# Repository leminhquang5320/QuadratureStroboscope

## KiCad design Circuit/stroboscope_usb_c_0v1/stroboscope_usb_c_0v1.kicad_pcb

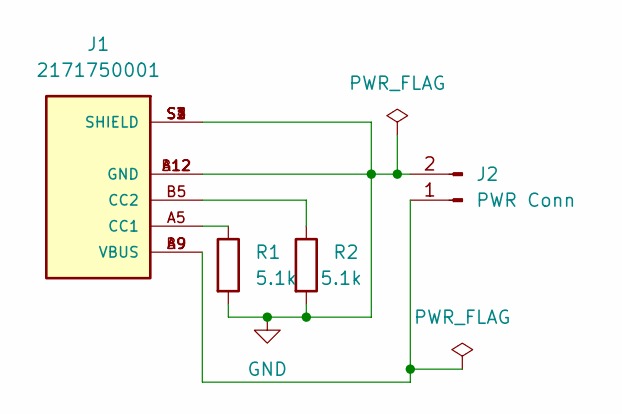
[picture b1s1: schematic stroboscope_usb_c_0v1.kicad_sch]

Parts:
J1: 2171750001; MOLEX_2171750001; PARTREV A1
J2: PWR Conn; JST_XH_B2B-XH-A_1x02_P2.50mm_Vertical
R1, R2: 5.1k; R_0805_2012Metric_Pad1.20x1.40mm_HandSolder

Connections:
GND: J1.A12 (GND), J1.B12 (GND), J1.S1 (SHIELD), J1.S2 (SHIELD), J1.S3 (SHIELD), J1.S4 (SHIELD), J2.2, R1.2, R2.2
unnamed: J1.A5 (CC1), R1.1
unnamed: J1.A9 (VBUS), J1.B9 (VBUS), J2.1
unnamed: J1.B5 (CC2), R2.1

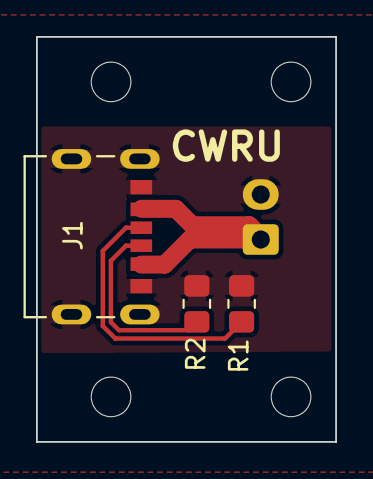
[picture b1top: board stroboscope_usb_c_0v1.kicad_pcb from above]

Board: 2 copper layers, 16.6 x 22.5 mm, 4 parts (1 on the bottom side), 4 nets.

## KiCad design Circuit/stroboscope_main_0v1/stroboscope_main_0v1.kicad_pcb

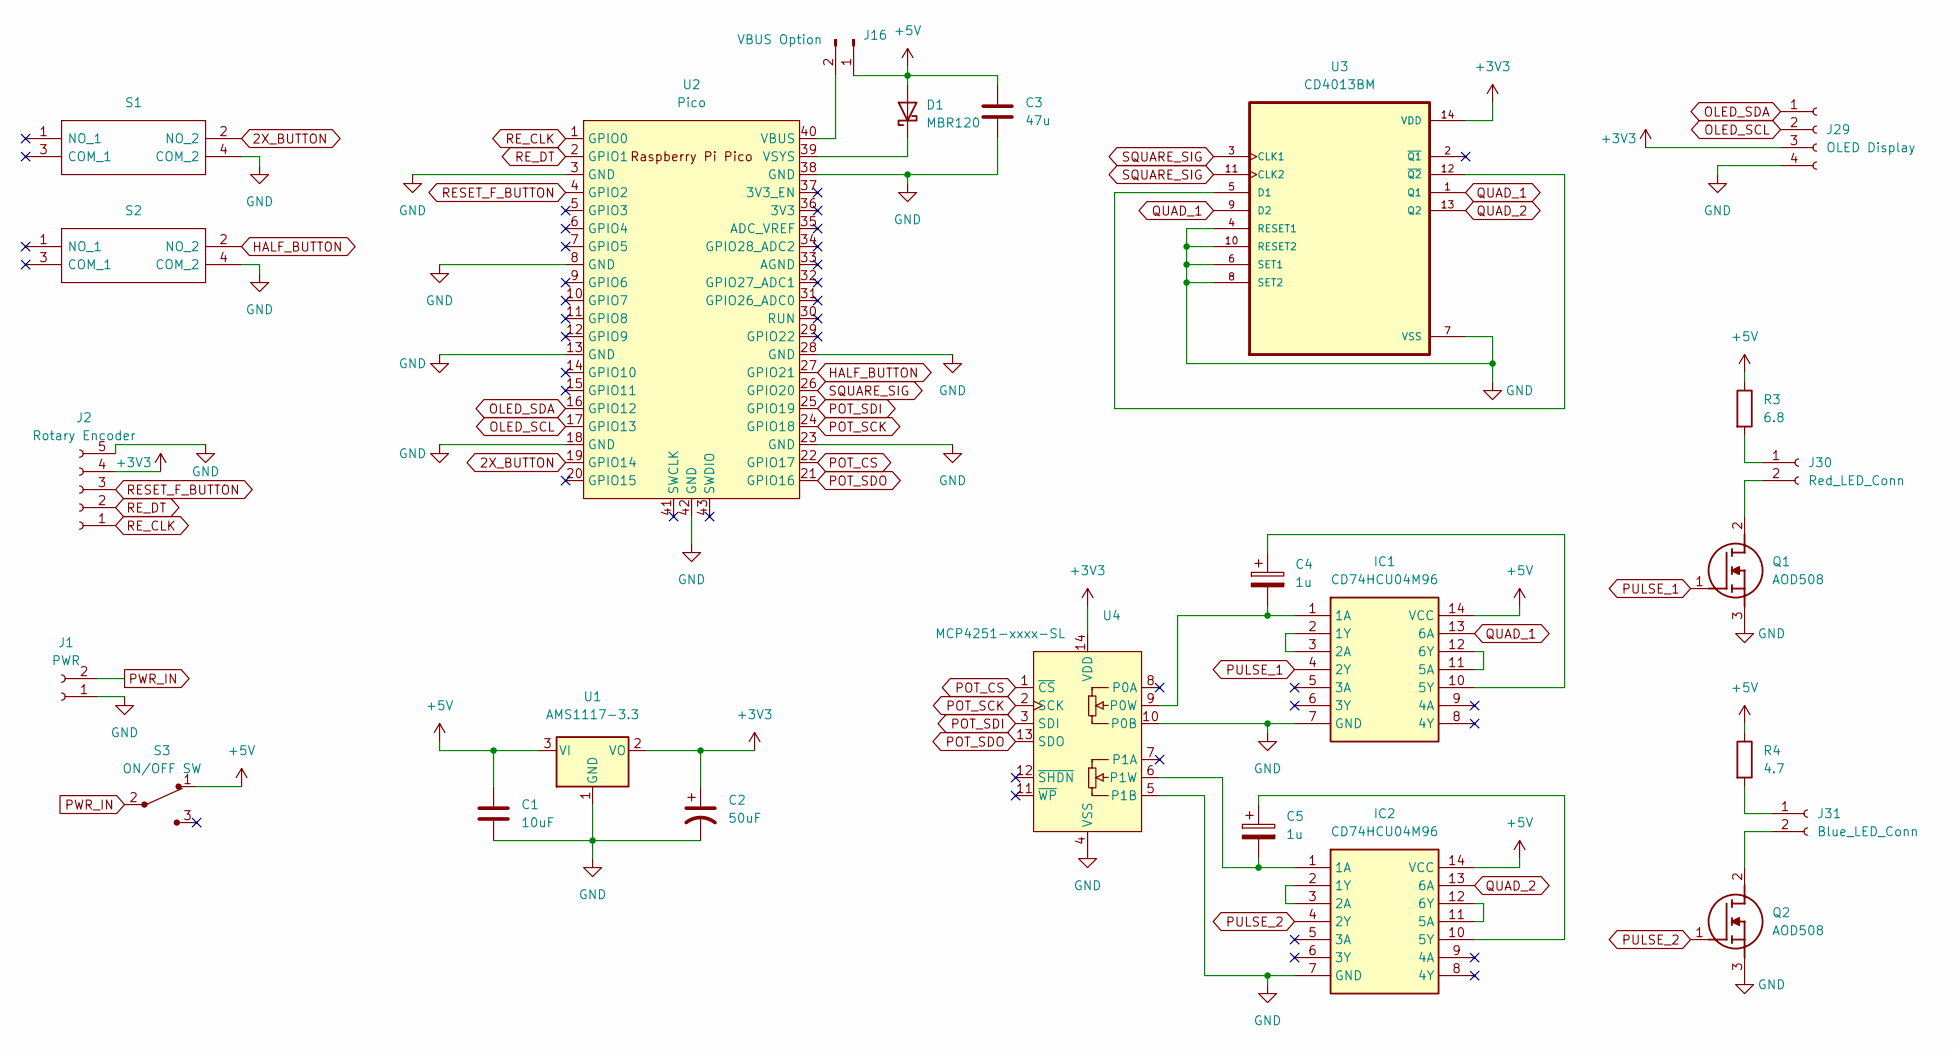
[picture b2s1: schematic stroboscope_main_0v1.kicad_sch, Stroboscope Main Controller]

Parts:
C1: 10uF; C_0603_1608Metric_Pad1.08x0.95mm_HandSolder
C2: 50uF; CP_Radial_D6.3mm_P2.50mm
C3: 47u; C_0603_1608Metric_Pad1.08x0.95mm_HandSolder
C4, C5: 1u; CP_Radial_D6.3mm_P2.50mm
D1: MBR120; D_SOD-123
IC1, IC2: CD74HCU04M96; SOIC127P600X175-14N; Manufacturer_Part_Number CD74HCU04M96; Mouser Part Number 595-CD74HCU04M96
J1: PWR; JST_XH_B2B-XH-A_1x02_P2.50mm_Vertical
J2: Rotary Encoder; PinHeader_1x05_P2.54mm_Vertical
J16: VBUS Option; PinHeader_1x02_P2.54mm_Vertical
J29: OLED Display; JST_XH_B4B-XH-A_1x04_P2.50mm_Vertical
J30: Red_LED_Conn; JST_XH_B2B-XH-A_1x02_P2.50mm_Vertical
J31: Blue_LED_Conn; JST_XH_B2B-XH-A_1x02_P2.50mm_Vertical
Q1, Q2: AOD508; Manufacturer_Part_Number AOD508
R3: 6.8; R_2512_6332Metric_Pad1.40x3.35mm_HandSolder
R4: 4.7; R_2512_6332Metric_Pad1.40x3.35mm_HandSolder
S1, S2: PTS125SM85-2_LFS; PTS125SM432LFS; Manufacturer_Part_Number PTS125SM85-2 LFS
S3: ON/OFF SW; Switch_Slide_11.6x4mm_EG1218; MPN EG1218; Digi-Key_PN EG1903-ND
U1: AMS1117-3.3; SOT-223-3_TabPin2
U2: Pico; RPi_Pico_SMD_TH
U3: CD4013BM; SOIC127P600X175-14N
U4: MCP4251-xxxx-SL; SOIC-14_3.9x8.7mm_P1.27mm

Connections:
2X_BUTTON: S1.2 (NO_2), U2.19 (GPIO14)
+3V3: C2.1, J2.4, J29.3, U1.2 (VO), U3.14 (VDD), U4.14 (VDD)
+5V: C1.1, C3.1, D1.2 (A), IC1.14 (VCC), IC2.14 (VCC), J16.1, R3.1, R4.1, S3.1, U1.3 (VI)
GND: C1.2, C2.2, C3.2, IC1.7 (GND), IC2.7 (GND), J1.1, J2.5, J29.4, Q1.3 (S), Q2.3 (S), S1.4 (COM_2), S2.4 (COM_2), U1.1 (GND), U2.3 (GND), U2.8 (GND), U2.13 (GND), U2.18 (GND), U2.23 (GND), U2.28 (GND), U2.38 (GND), U2.42 (GND), U3.4 (RESET1), U3.6 (SET1), U3.7 (VSS), U3.8 (SET2), U3.10 (RESET2), U4.4 (VSS), U4.5 (P1B), U4.10 (P0B)
HALF_BUTTON: S2.2 (NO_2), U2.27 (GPIO21)
unnamed: D1.1 (K), U2.39 (VSYS)
unnamed: C4.2, IC1.1 (1A), U4.9 (P0W)
unnamed: IC1.2 (1Y), IC1.3 (2A)
unnamed: C4.1, IC1.10 (5Y)
unnamed: IC1.11 (5A), IC1.12 (6Y)
unnamed: C5.2, IC2.1 (1A), U4.6 (P1W)
unnamed: IC2.2 (1Y), IC2.3 (2A)
unnamed: C5.1, IC2.10 (5Y)
unnamed: IC2.11 (5A), IC2.12 (6Y)
unnamed: J16.2, U2.40 (VBUS)
unnamed: J30.1, R3.2
unnamed: J30.2, Q1.2 (D)
unnamed: J31.1, R4.2
unnamed: J31.2, Q2.2 (D)
unnamed: U3.5 (D1), U3.12 (~Q2)
OLED_SCL: J29.2, U2.17 (GPIO13)
OLED_SDA: J29.1, U2.16 (GPIO12)
POT_CS: U2.22 (GPIO17), U4.1 (~CS)
POT_SCK: U2.24 (GPIO18), U4.2 (SCK)
POT_SDI: U2.25 (GPIO19), U4.3 (SDI)
POT_SDO: U2.21 (GPIO16), U4.13 (SDO)
PULSE_1: IC1.4 (2Y), Q1.1 (G)
PULSE_2: IC2.4 (2Y), Q2.1 (G)
PWR_IN: J1.2, S3.2
QUAD_1: IC1.13 (6A), U3.1 (Q1), U3.9 (D2)
QUAD_2: IC2.13 (6A), U3.13 (Q2)
RESET_F_BUTTON: J2.3, U2.4 (GPIO2)
RE_CLK: J2.1, U2.1 (GPIO0)
RE_DT: J2.2, U2.2 (GPIO1)
SQUARE_SIG: U2.26 (GPIO20), U3.3 (CLK1), U3.11 (CLK2)

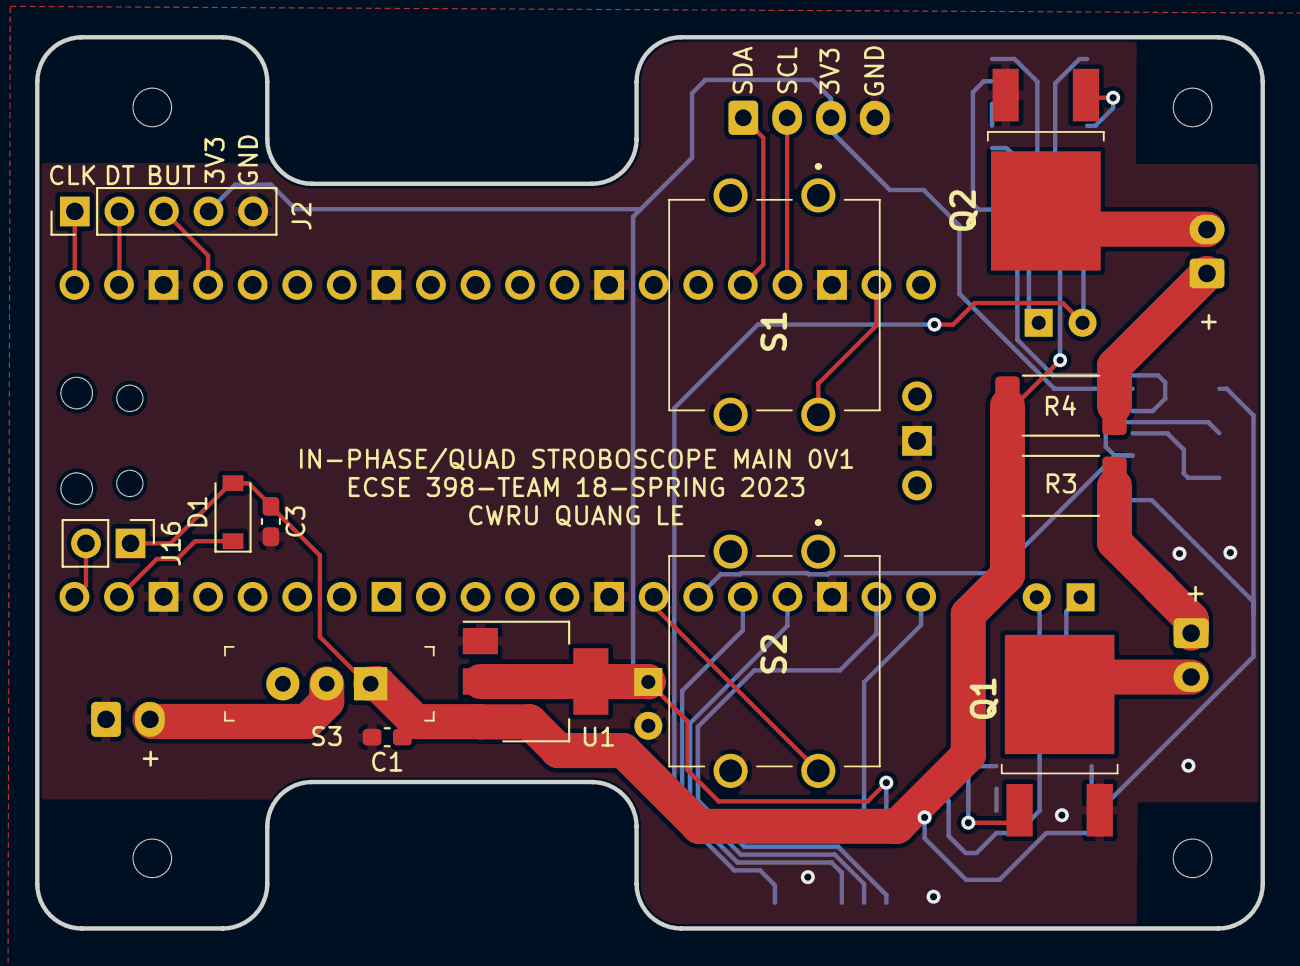
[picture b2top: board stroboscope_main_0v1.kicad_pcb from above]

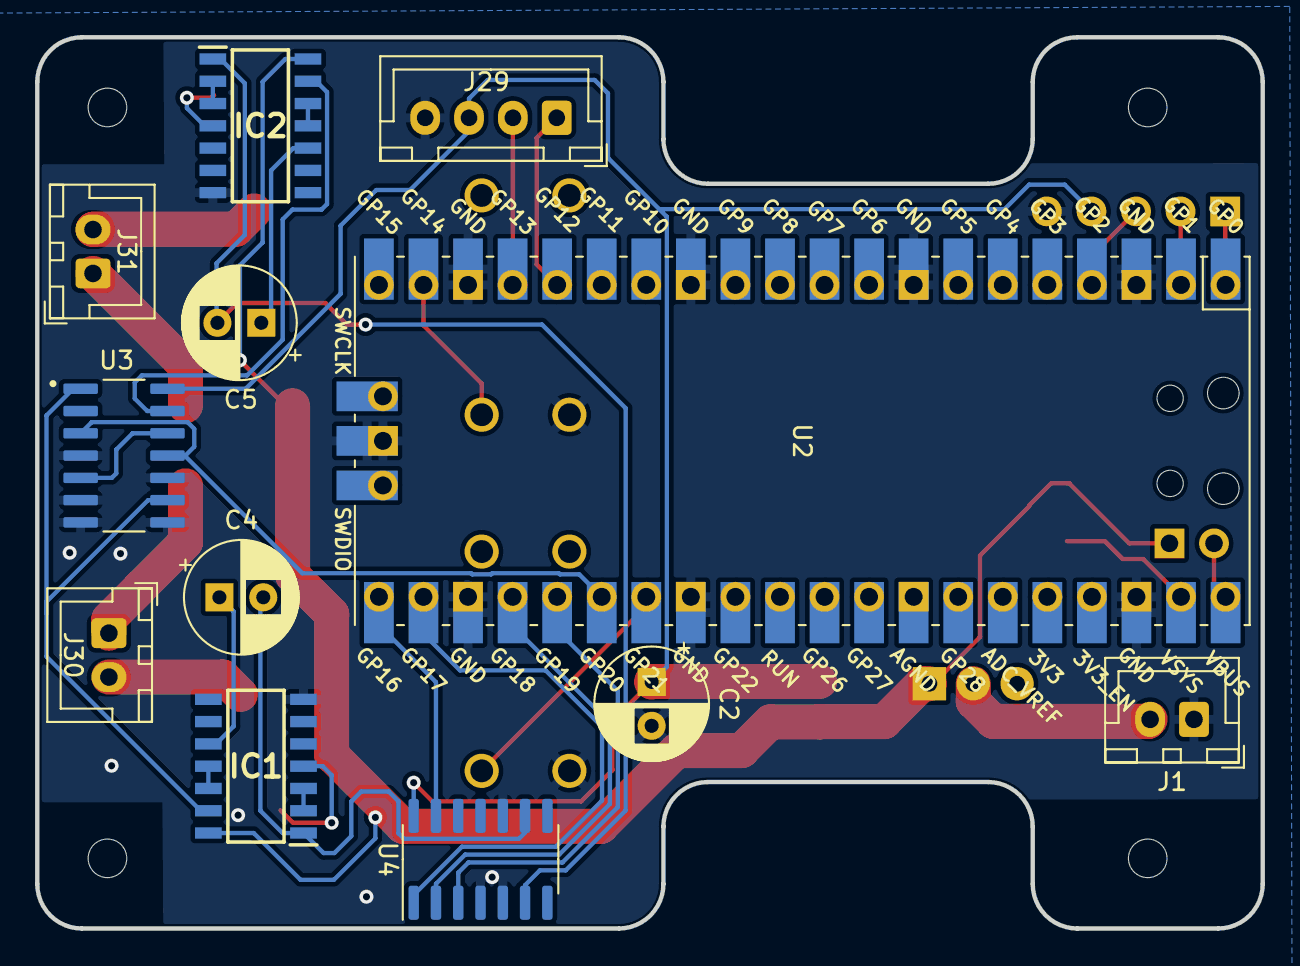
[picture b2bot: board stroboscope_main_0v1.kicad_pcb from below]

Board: 2 copper layers, 69.8 x 50.8 mm, 25 parts (12 on the bottom side), 35 nets.

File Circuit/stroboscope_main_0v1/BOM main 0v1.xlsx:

Id | Designator | Package | Quantity | Designation | Supplier and ref | Column1 | _1
1 | J16 | PinHeader_1x02_P2.54mm_Vertical | 1 | VBUS Option
2 | REF**,REF**,REF**,REF** | MountingHole_2.2mm_M2 | 4 | MountingHole_2.2mm_M2
3 | S1,S2 | PTS125SM432LFS | 2 | PTS125SM85-2_LFS
4 | S3 | Switch_Slide_11.6x4mm_EG1218 | 1 | ON/OFF SW
5 | D1 | D_SOD-123 | 1 | MBR120
6 | Q2,Q1 | AOD508 | 2 | AOD508
7 | U1 | SOT-223-3_TabPin2 | 1 | AMS1117-3.3
8 | J2 | PinHeader_1x05_P2.54mm_Vertical | 1 | Rotary Encoder
9 | R4 | R_2512_6332Metric_Pad1.40x3.35mm_HandSolder | 1 | 4.7
10 | C3 | C_0603_1608Metric_Pad1.08x0.95mm_HandSolder | 1 | 47u
11 | R3 | R_2512_6332Metric_Pad1.40x3.35mm_HandSolder | 1 | 6.8
12 | C1 | C_0603_1608Metric_Pad1.08x0.95mm_HandSolder | 1 | 10uF
13 | IC2,IC1 | SOIC127P600X175-14N | 2 | CD74HCU04M96
14 | U3 | SOIC127P600X175-14N | 1 | CD4013BM
15 | U4 | SOIC-14_3.9x8.7mm_P1.27mm | 1 | MCP4251-xxxx-SL
16 | J1 | JST_XH_B2B-XH-A_1x02_P2.50mm_Vertical | 1 | PWR
17 | C2 | CP_Radial_D6.3mm_P2.50mm | 1 | 50uF
18 | J29 | JST_XH_B4B-XH-A_1x04_P2.50mm_Vertical | 1 | OLED Display
19 | J30 | JST_XH_B2B-XH-A_1x02_P2.50mm_Vertical | 1 | Red_LED_Conn
20 | C4,C5 | CP_Radial_D6.3mm_P2.50mm | 2 | 1u
21 | J31 | JST_XH_B2B-XH-A_1x02_P2.50mm_Vertical | 1 | Blue_LED_Conn
22 | U2 | RPi_Pico_SMD_TH | 1 | Pico
